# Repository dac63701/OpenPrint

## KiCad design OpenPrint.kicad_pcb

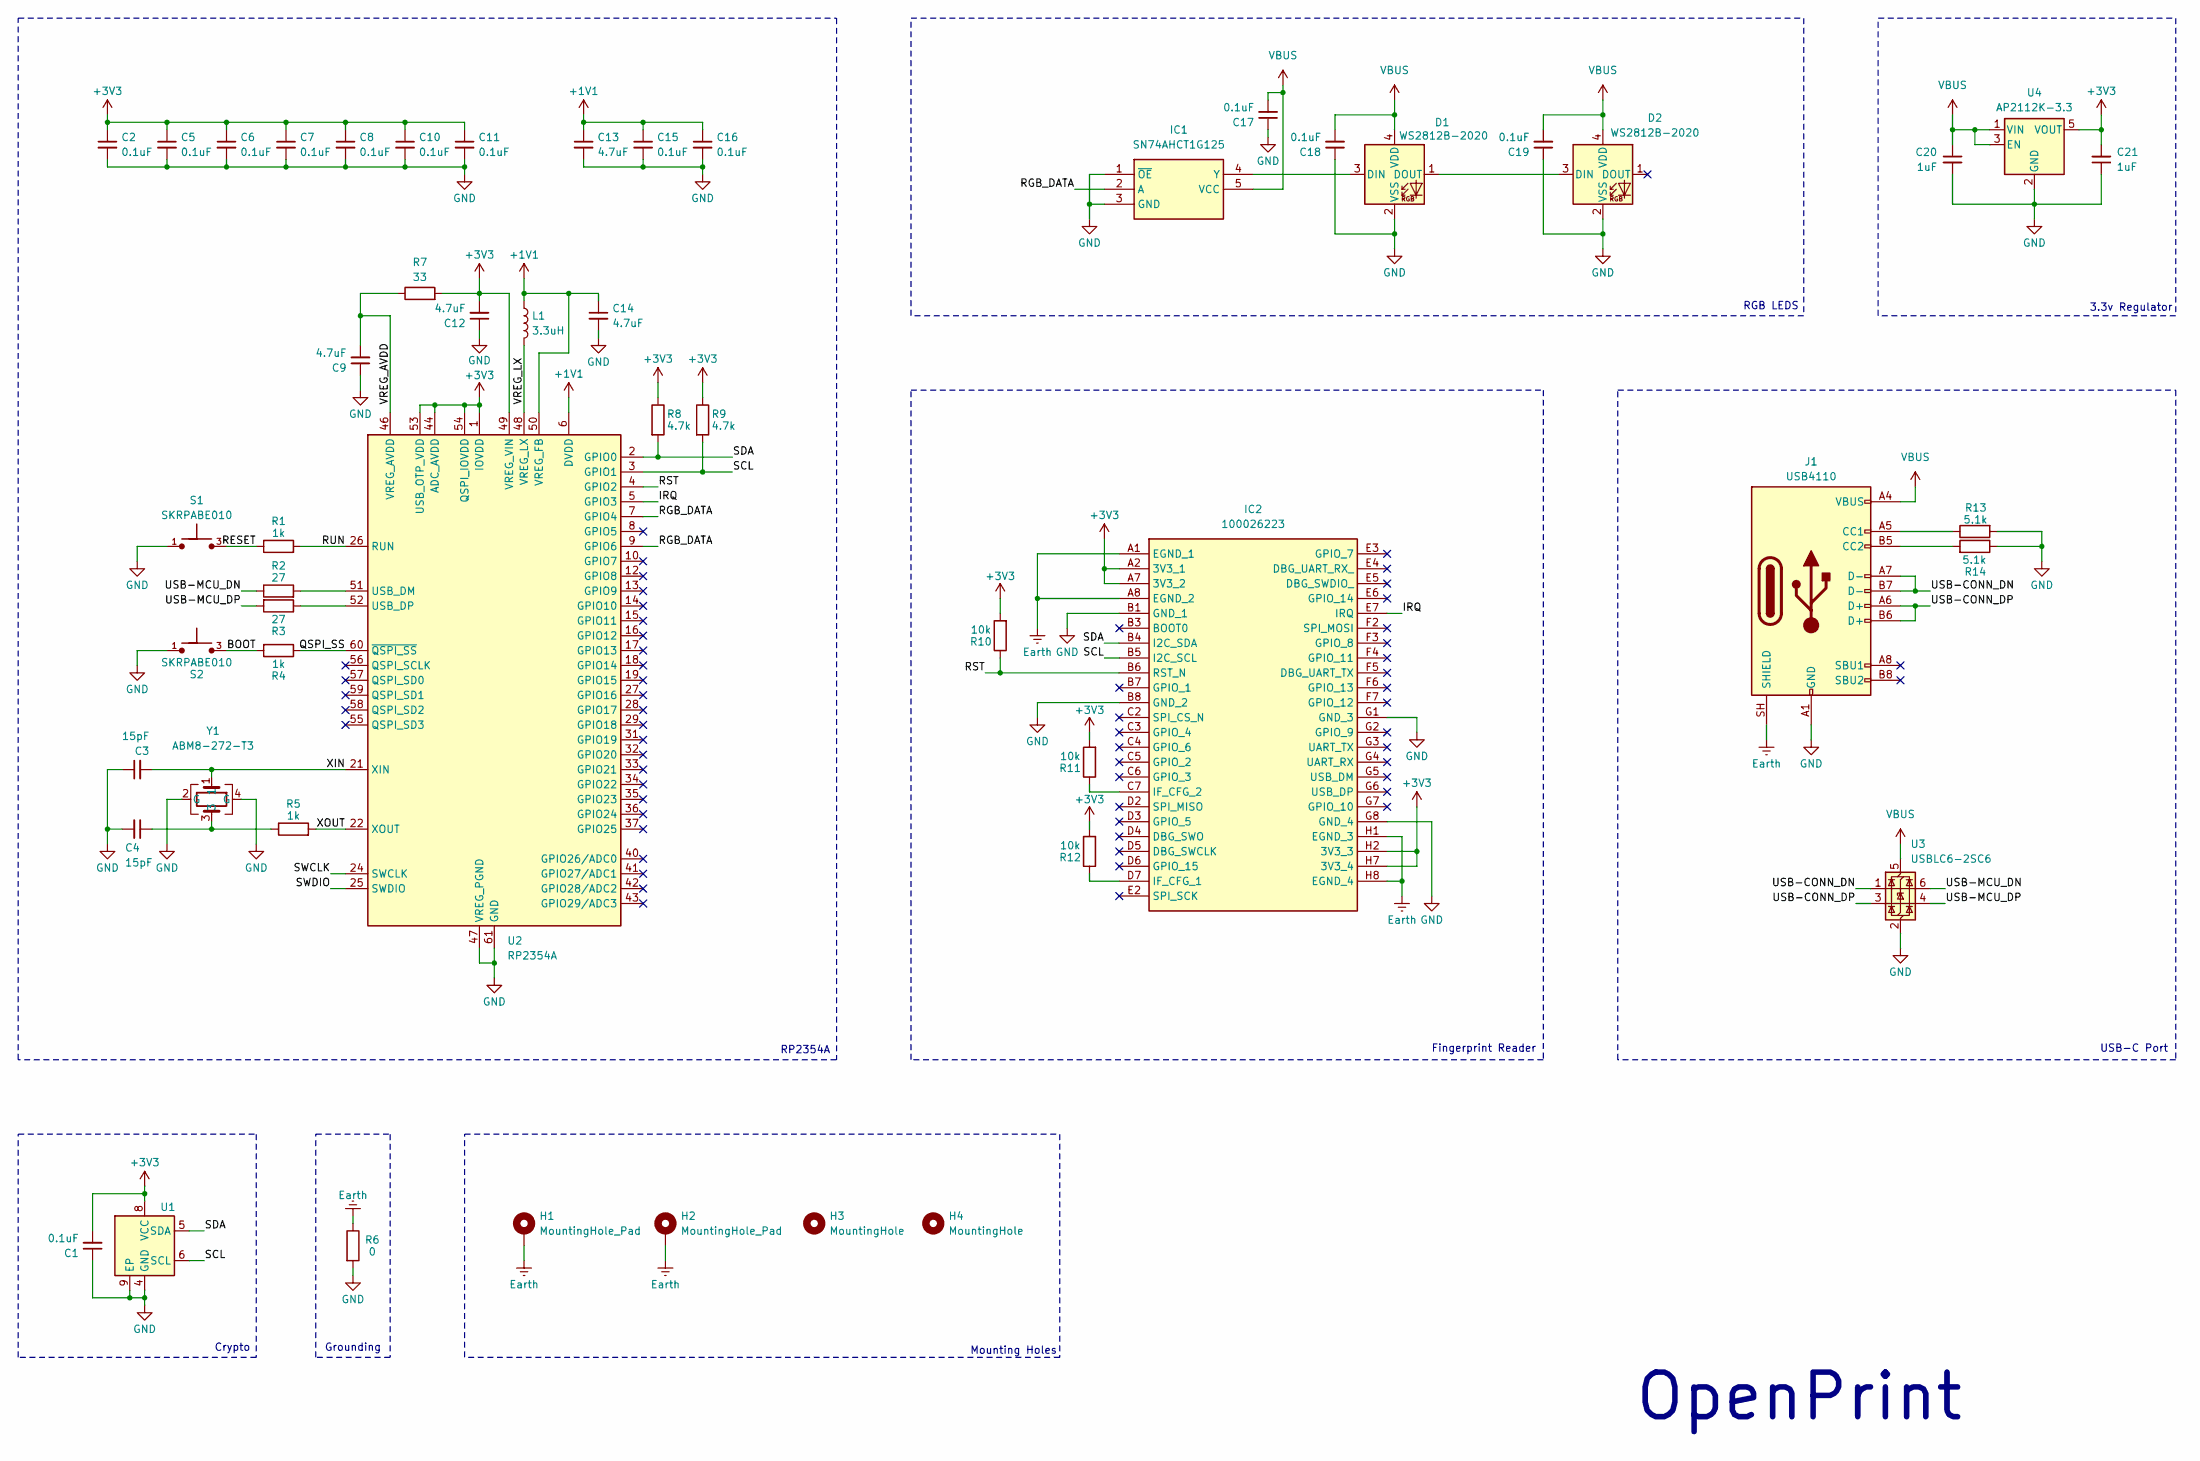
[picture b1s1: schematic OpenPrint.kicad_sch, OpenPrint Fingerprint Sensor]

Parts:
C1, C2, C5, C6, C7, C8, C10, C11, C15, C16, C17, C18, C19: 0.1uF; C_0402_1005Metric
C3, C4: 15pF; C_0402_1005Metric
C9, C12, C13, C14: 4.7uF; C_0402_1005Metric
C20, C21: 1uF; C_0402_1005Metric
D1, D2: WS2812B-2020; LED_WS2812B-2020_PLCC4_2.0x2.0mm
H1, H2: MountingHole_Pad; MountingHole_2.2mm_M2_Pad
H3, H4: MountingHole; MountingHole_2mm
IC1: SN74AHCT1G125; SOT95P280X145-5N; Mouser Part Number 595-SNAHCT1G125DBVR
IC2: 100026223; Manufacturer_Part_Number 100026223
J1: USB4110; USB_C_Receptacle_GCT_USB4110
L1: 3.3uH; L_0805_2012Metric
R1, R4, R5: 1k; R_0402_1005Metric
R2, R3: 27; R_0402_1005Metric
R6: 0; C_0402_1005Metric
R7: 33; R_0402_1005Metric
R8, R9: 4.7k; C_0402_1005Metric
R10, R11, R12: 10k; R_0402_1005Metric
R13, R14: 5.1k; R_0402_1005Metric
S1, S2: SKRPABE010; SW_SKRPABE010
U1: ATECC608C-MAHDA; DFN-8-1EP_3x2mm_P0.5mm_EP1.3x1.5mm
U2: RP2354A; QFN-60-1EP_7x7mm_P0.4mm_EP3.4x3.4mm
U3: USBLC6-2SC6; SOT-23-6
U4: AP2112K-3.3; SOT-23-5
Y1: ABM8-272-T3; ABM8272T3; Mouser Part Number 815-ABM8-272-T3

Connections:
+1V1: C13.1, C14.1, C15.1, C16.1, L1.1, U2.6 (DVDD), U2.23 (DVDD), U2.39 (DVDD), U2.50 (VREG_FB)
+3V3: C1.2, C2.1, C5.1, C6.1, C7.1, C8.1, C10.1, C11.1, C12.2, C21.2, IC2.A2 (3V3_1), IC2.A7 (3V3_2), IC2.H2 (3V3_3), IC2.H7 (3V3_4), R7.2, R8.1, R9.1, R10.2, R11.2, R12.2, U1.8 (VCC), U2.1 (IOVDD), U2.11 (IOVDD), U2.20 (IOVDD), U2.30 (IOVDD), U2.38 (IOVDD), U2.44 (ADC_AVDD), U2.45 (IOVDD), U2.49 (VREG_VIN), U2.53 (USB_OTP_VDD), U2.54 (QSPI_IOVDD), U4.5 (VOUT)
/BOOT: R4.2, S2.3, S2.4
/IRQ: IC2.E7 (IRQ), U2.5 (GPIO3)
/QSPI_SS: R4.1, U2.60 (~QSPI_SS)
/RESET: R1.1, S1.3, S1.4
/RGB_DATA: IC1.2 (A), U2.7 (GPIO4), U2.9 (GPIO6)
/RST: IC2.B6 (RST_N), R10.1, U2.4 (GPIO2)
/RUN: R1.2, U2.26 (RUN)
/SCL: IC2.B5 (I2C_SCL), R9.2, U1.6 (SCL), U2.3 (GPIO1)
/SDA: IC2.B4 (I2C_SDA), R8.2, U1.5 (SDA), U2.2 (GPIO0)
/SWCLK: U2.24 (SWCLK)
/SWDIO: U2.25 (SWDIO)
/USB-CONN_DN: J1.A7 (D-), J1.B7 (D-), U3.1 (I/O1)
/USB-CONN_DP: J1.A6 (D+), J1.B6 (D+), U3.3 (I/O2)
/USB-MCU_DN: R2.1, U3.6 (I/O1)
/USB-MCU_DP: R3.2, U3.4 (I/O2)
/VREG_AVDD: C9.2, R7.1, U2.46 (VREG_AVDD)
/VREG_LX: L1.2, U2.48 (VREG_LX)
/XIN: C3.2, U2.21 (XIN), Y1.1
/XOUT: R5.2, U2.22 (XOUT)
Earth: H1.1 (1_1), H2.1 (1_1), IC2.A1 (EGND_1), IC2.A8 (EGND_2), IC2.H1 (EGND_3), IC2.H8 (EGND_4), J1.SH (SHIELD), R6.1
GND: C1.1, C2.2, C3.1, C4.2, C5.2, C6.2, C7.2, C8.2, C9.1, C10.2, C11.2, C12.1, C13.2, C14.2, C15.2, C16.2, C17.1, C18.1, C19.1, C20.2, C21.1, D1.2 (VSS), D2.2 (VSS), IC1.1 (~OE), IC1.3 (GND), IC2.B1 (GND_1), IC2.B8 (GND_2), IC2.G1 (GND_3), IC2.G8 (GND_4), J1.A1 (GND), J1.A12 (GND), J1.B1 (GND), J1.B12 (GND), R6.2, R13.2, R14.1, S1.1, S1.2, S2.1, S2.2, U1.4 (GND), U1.9 (EP), U2.47 (VREG_PGND), U2.61 (GND), U3.2 (GND), U4.2 (GND), Y1.2 (G), Y1.4 (G)
unnamed: C4.1, R5.1, Y1.3
unnamed: D1.3 (DIN), IC1.4 (Y)
unnamed: D1.1 (DOUT), D2.3 (DIN)
unnamed: IC2.D7 (IF_CFG_1), R12.1
unnamed: IC2.C7 (IF_CFG_2), R11.1
unnamed: J1.A5 (CC1), R13.1
unnamed: J1.B5 (CC2), R14.2
unnamed: R2.2, U2.51 (USB_DM)
unnamed: R3.1, U2.52 (USB_DP)
VBUS: C17.2, C18.2, C19.2, C20.1, D1.4 (VDD), D2.4 (VDD), IC1.5 (VCC), J1.A4 (VBUS), J1.A9 (VBUS), J1.B4 (VBUS), J1.B9 (VBUS), U3.5 (VBUS), U4.1 (VIN), U4.3 (EN)

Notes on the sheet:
OpenPrint
USB-C Port
3.3v Regulator
Grounding
Fingerprint Reader
RP2354A
RGB LEDS
Crypto
Mounting Holes

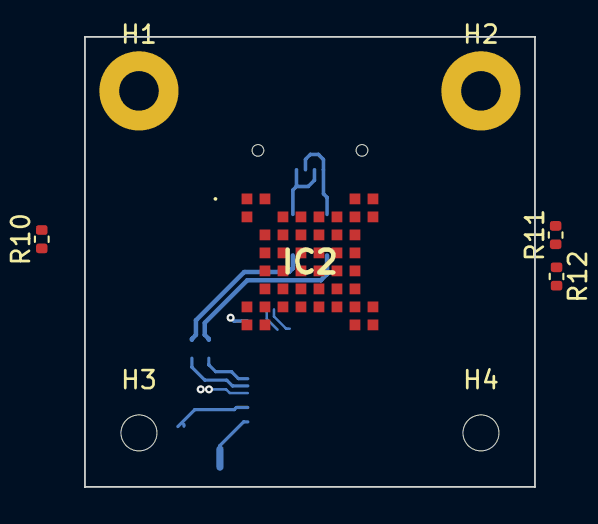
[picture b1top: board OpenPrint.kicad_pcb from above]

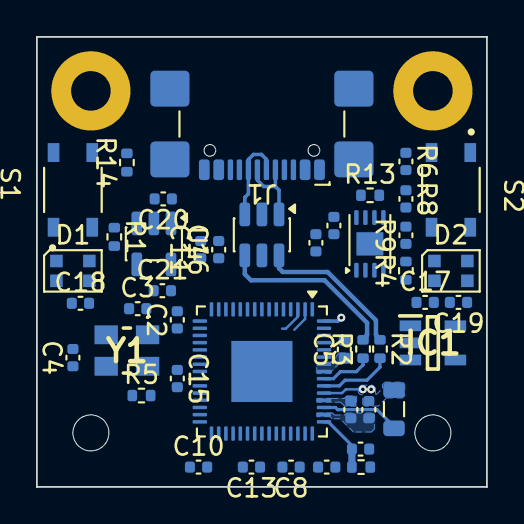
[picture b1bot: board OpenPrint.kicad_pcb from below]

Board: 4 copper layers, 25.0 x 25.0 mm, 52 parts (44 on the bottom side), 31 nets.
